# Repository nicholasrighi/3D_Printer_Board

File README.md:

# 3D_Printer_Board

Circuit board layout for 3D printer control board and partial 3D printer control code.

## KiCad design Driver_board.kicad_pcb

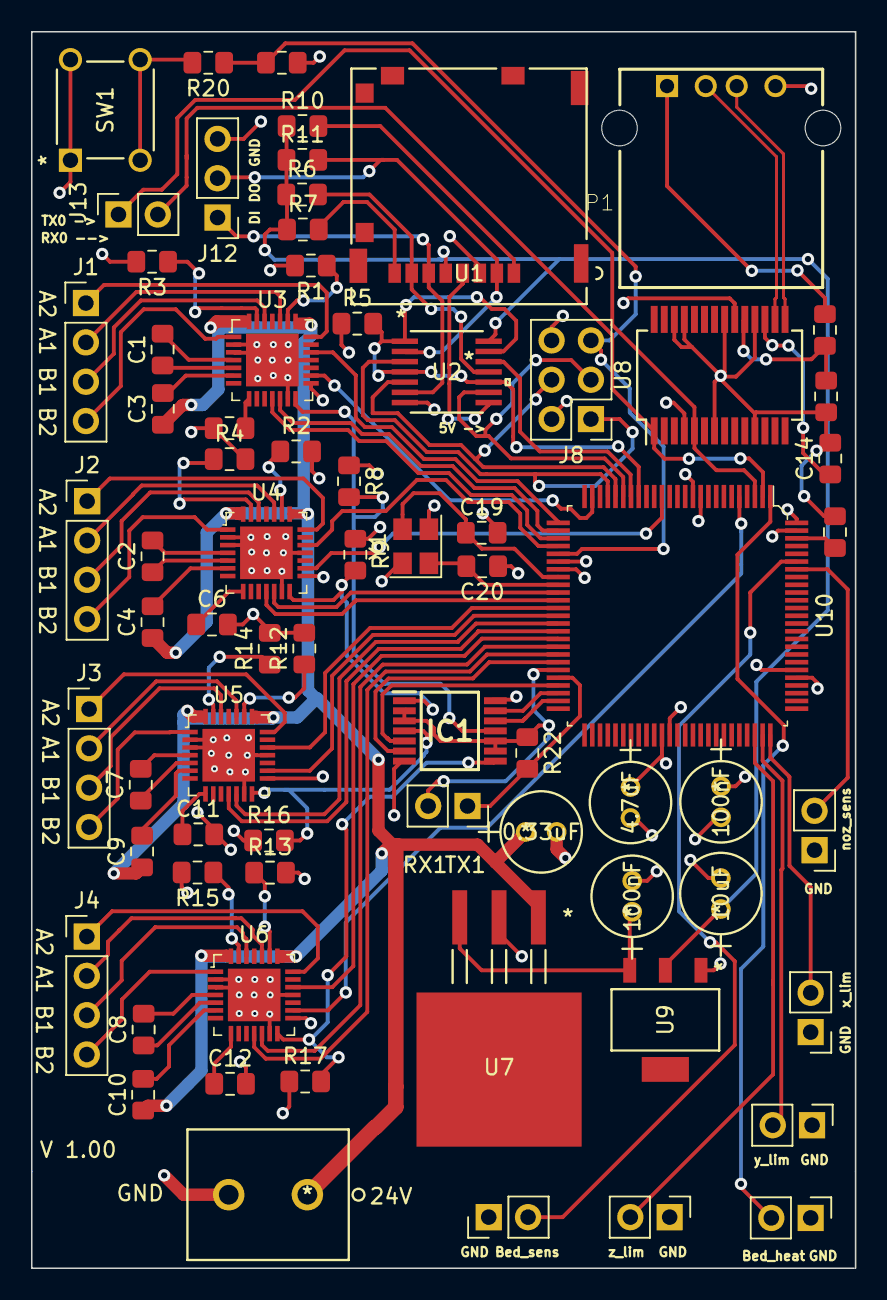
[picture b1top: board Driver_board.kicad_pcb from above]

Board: 4 copper layers, 53.2 x 79.8 mm, 72 parts (0 on the bottom side), 99 nets.

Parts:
C1, C2, C7, C8: 22nF; C_0805_2012Metric_Pad1.15x1.40mm_HandSolder
C3, C4, C9, C10, C14, C21: 100nF; C_0805_2012Metric_Pad1.15x1.40mm_HandSolder
C5, C6, C11, C12: 2.2uF; C_0805_2012Metric_Pad1.15x1.40mm_HandSolder
C13: 0.33uF; alum_electro_cap
C15, C16: 100nF; alum_electro_cap
C17: 4.7uF; alum_electro_cap
C18: 10uF; alum_electro_cap
C19, C20: 20pF; C_0805_2012Metric_Pad1.15x1.40mm_HandSolder
IC1: 74HC4066PW,118; SOP65P640X110-14N
J1, J2, J3, J4: Conn_01x04_Female; PinHeader_1x04_P2.54mm_Vertical
J5, J6, J7, J9, J10, J11: Conn_01x02; PinHeader_1x02_P2.54mm_Vertical
J8: AVR-ISP-6; PinHeader_2x03_P2.54mm_Vertical
J12: Conn_01x03_Female; PinHeader_1x03_P2.54mm_Vertical
J13, J14: Conn_01x02_Female; PinSocket_1x02_P2.54mm_Vertical
J15: Conn_01x02_Female; 282837-2_power_connector
P1: USB-A1HSW6; OST_USB-A1HSW6
R1, R2, R3, R4, R12, R13, R14, R15: 180m; R_0805_2012Metric_Pad1.15x1.40mm_HandSolder
R5, R19: 10k; R_0805_2012Metric_Pad1.15x1.40mm_HandSolder
R6, R7, R10, R11: 50k; R_0805_2012Metric_Pad1.15x1.40mm_HandSolder
R8, R9, R16, R17: 22k; R_0805_2012Metric_Pad1.15x1.40mm_HandSolder
R18, R21: 4.7k; R_0805_2012Metric_Pad1.15x1.40mm_HandSolder
R20: 330; R_0805_2012Metric_Pad1.15x1.40mm_HandSolder
R22: 1k; R_0805_2012Metric_Pad1.15x1.40mm_HandSolder
SW1: 1825910-2; 1825910-2_pushbutton
U1: 503182-1852
U2: 74LCX125MTCX
U3, U4, U5, U6: TMC2208-LA-T; VFQFN-28-1EP_5x5mm
U7: uA7805; UA7805CKTTR
U8: FT232RL; SSOP-28_5.3x10.2mm_P0.65mm
U9: LM1117-3.3; LM1117IMP-3.3&slash_NOPB
U10: ATMEGA2560-16AU; TQFP-100_14x14mm
Y1: Crystal_GND24; Crystal_SMD_3225-4Pin_3.2x2.5mm

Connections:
+3V3: C18.1, R6.1, R7.1, R10.1, R11.1, U1.4, U2.14, U9.2
+5V: C15.1, C16.1, C17.1, IC1.14, J8.2, R5.1, R8.1, R9.1, R16.1, R17.1, R21.1, U3.15, U4.15, U5.15, U6.15, U7.3, U8.4, U8.20, U9.3, U10.10, U10.31, U10.61, U10.80, U10.100
+24V: C3.1, C4.1, C9.1, C10.1, C13.1, J15.1, U3.22, U3.28, U4.22, U4.28, U5.22, U5.28, U6.22, U6.28, U7.1
/CPO_1: C1.2, U3.4
/CPO_2: C2.2, U4.4
/CPO_3: C7.2, U5.4
/CPO_4: C8.2, U6.4
/CS: U2.12, U10.19
/DIAG1: U3.11, U10.28
/DIAG2: U4.11, U10.36
/DIAG3: U5.11, U10.40
/DIAG4: U6.11, U10.43
/DIR1: U3.19, U10.26
/DIR2: U4.19, U10.29
/DIR3: U5.19, U10.37
/DIR4: U6.19, U10.41
/Heated_bed: J9.2, U10.1
/Heated_bed_sensor: J11.2, U10.95
/INDEX1: U3.12, U10.27
/INDEX2: U4.12, U10.35
/INDEX3: U5.12, U10.39
/INDEX4: U6.12, U10.42
/MISO: J8.1, U2.3, U10.22
/MOSI: J8.4, U2.5, U10.21
/OA1_1: J1.2, U3.24
/OA1_2: J2.2, U4.24
/OA1_3: J3.2, U5.24
/OA1_4: J4.2, U6.24
/OA2_1: J1.1, U3.21
/OA2_2: J2.1, U4.21
/OA2_3: J3.1, U5.21
/OA2_4: J4.1, U6.21
/OB1_1: J1.3, U3.26
/OB1_2: J2.3, U4.26
/OB1_3: J3.3, U5.26
/OB1_4: J4.3, U6.26
/OB2_1: J1.4, U3.1
/OB2_2: J2.4, U4.1
/OB2_3: J3.4, U5.1
/OB2_4: J4.4, U6.1
/RST: J8.5, R20.1, R21.2, U10.30
/RX0: J13.2, U8.1, U10.2
/RX1: IC1.2, IC1.3, IC1.9, IC1.10, J14.2, R22.1, U10.45
/SCK: J8.3, U2.9, U10.20
/SD_DI: J12.1, U1.3, U2.6
/SD_DO: J12.2, R11.2, U1.7, U2.2
/SD_clk: U1.5, U2.8
/SD_connect: R5.2, U2.1, U2.4, U2.10, U2.13, U10.18
/SD_select: R6.2, U1.2, U2.11
/STEP1: U3.16, U10.24
/STEP2: U4.16, U10.15
/STEP3: U5.16, U10.38
/STEP4: U6.16, U10.5
/TMC_ENABLE1: IC1.12, U10.49
/TMC_ENABLE2: IC1.13, U10.48
/TMC_ENABLE3: IC1.5, U10.47
/TMC_ENABLE4: IC1.6, U10.44
/TMC_TX1: IC1.11, R8.2, U3.14
/TMC_TX2: IC1.1, R9.2, U4.14
/TMC_TX3: IC1.4, R16.2, U5.14
/TMC_TX4: IC1.8, R17.2, U6.14
/TX0: J13.1, U8.5, U10.3
/TX1: J14.1, R22.2, U10.46
/Temp_sensor: J10.2, U10.94
/USBD+: P1.3, U8.15
/USBD-: P1.2, U8.16
/VCP_1: C3.2, U3.6
/VCP_2: C4.2, U4.6
/VCP_3: C9.2, U5.6
/VCP_4: C10.2, U6.6
/X_limit: J5.2, U10.75
/Y_limit: J7.2, U10.74
/Z_limit: J6.2, U10.73
GND: C5.2, C6.2, C11.2, C12.2, C13.2, C14.2, C15.2, C16.2, C17.2, C18.2, C19.2, C20.1, C21.2, IC1.7, J5.1, J6.1, J7.1, J8.6, J9.1, J10.1, J11.1, J12.3, J15.2, P1.4, R1.2, R2.2, R3.2, R4.2, R12.2, R13.2, R14.2, R15.2, R19.2, SW1.1, SW1.2, U1.6, U2.7, U3.2, U3.3, U3.13, U3.18, U3.29, U4.2, U4.3, U4.13, U4.18, U4.29, U5.2, U5.3, U5.13, U5.18, U5.29, U6.2, U6.3, U6.13, U6.18, U6.29, U7.2, U8.7, U8.11, U8.18, U8.21, U8.25, U8.26, U9.1, U10.11, U10.32, U10.62, U10.81, U10.99, Y1.2, Y1.4
unnamed: C1.1, U3.5
unnamed: C2.1, U4.5
unnamed: C5.1, U3.8
unnamed: C6.1, U4.8
unnamed: C7.1, U5.5
unnamed: C8.1, U6.5
unnamed: C11.1, U5.8
unnamed: C12.1, U6.8
unnamed: C14.1, U8.17
unnamed: C19.1, U10.33, Y1.3
unnamed: C20.2, U10.34, Y1.1
unnamed: C21.1, U10.98
unnamed: P1.1, R18.1
unnamed: R1.1, U3.23
unnamed: R2.1, U4.23
unnamed: R3.1, U3.27
unnamed: R4.1, U4.27
unnamed: R7.2, U1.1
unnamed: R10.2, U1.8
unnamed: R12.1, U5.23
unnamed: R13.1, U6.23
unnamed: R14.1, U5.27
unnamed: R15.1, U6.27
unnamed: R18.2, R19.1, U8.19
unnamed: R20.2, SW1.3, SW1.4

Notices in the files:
parts and their libraries:
Copyright 2016 Accelerated Designs. All rights reserved.
